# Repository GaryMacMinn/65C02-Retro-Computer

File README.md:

# 65C02-Retro-Computer
A retro computer system based on the 65C02 CPU in a modular format.

This is my first version of a retro 65C02 based comnputer. My original design for this project
was around a single board containing all of the parts (a single board computer!!). After a bit of an
initial draw up, I realised that there were a lot of unknown details to the design and if I needed to change anything it would mean producing an entire new PCB. After a little thought I decided to do a backplane design that allows sections and functionality to be plugged in as required. If I wanted to remove or change any
sections I could just redo that plug in card rather that everything. 

The system at present consists of:
* Backplane Board
* Power Supply and Reset Card
* CPU Card
* Memory Card (Combined Flash Memory and SRAM)
* Serial Card
* Parallel Card

The files included in the Schematic & PCB directory are the KiCAD schematic and PCB files as they stand
at the moment. These cards have been finalised, produced and tested. The others will be added as I build
and verify their designs.

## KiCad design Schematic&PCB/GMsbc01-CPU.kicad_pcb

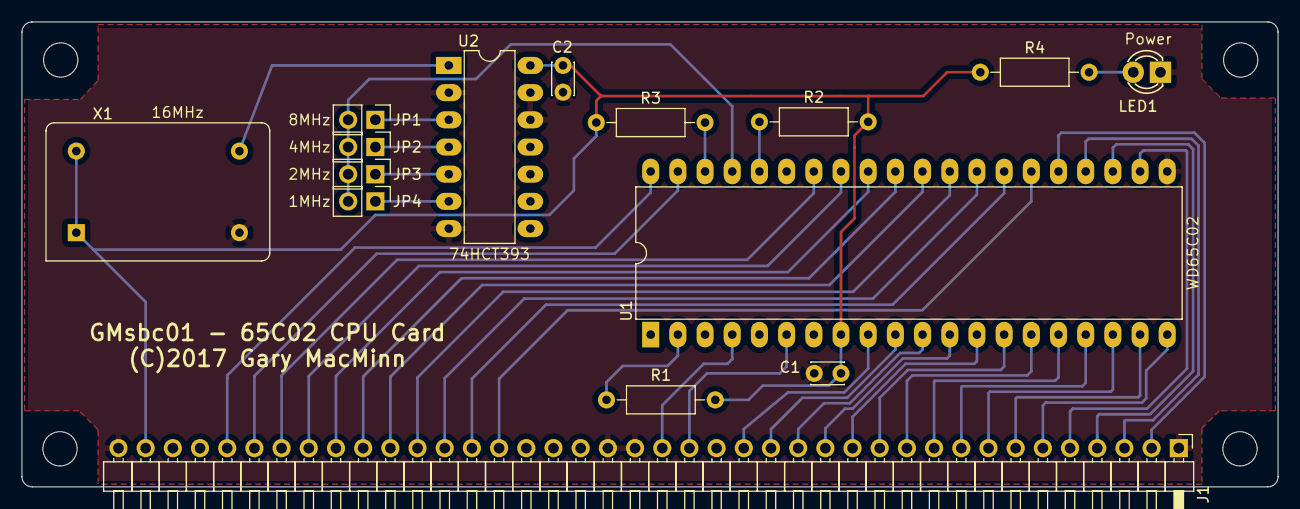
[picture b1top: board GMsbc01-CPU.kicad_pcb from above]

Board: 2 copper layers, 117.3 x 43.4 mm, 19 parts (0 on the bottom side), 41 nets.

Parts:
1, 2, 3, 4: MountingHole_3.2mm_M3
C1, C2: 0.1uF; C_Disc_D3.0mm_W2.0mm_P2.50mm
J1: CONN_01X40; Pin_Header_Angled_1x40_Pitch2.54mm
JP1: 8MHz; Pin_Header_Straight_1x02_Pitch2.54mm
JP2: 4MHz; Pin_Header_Straight_1x02_Pitch2.54mm
JP3: 2MHz; Pin_Header_Straight_1x02_Pitch2.54mm
JP4: 1MHz; Pin_Header_Straight_1x02_Pitch2.54mm
LED1: Power; LED-3MM
R1, R2, R3: 3k3; R_Axial_DIN0207_L6.3mm_D2.5mm_P10.16mm_Horizontal
R4: 330R; R_Axial_DIN0207_L6.3mm_D2.5mm_P10.16mm_Horizontal
U1: WD65C02; DIP-40_W15.24mm_LongPads
U2: 74HCT393; DIP-14_W7.62mm_LongPads
X1: 16MHz; Oscillator_DIP-14

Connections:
+5v: C1.1, C2.1, J1.39, R1.2, R2.2, R3.2, R4.2, U1.8, U2.14, X1.1, X1.14
/IRQ: J1.20, U1.4
/NMI: J1.19, U1.6
/Reset: J1.36, U1.40
A0: J1.17, U1.9
A1: J1.16, U1.10
A2: J1.15, U1.11
A3: J1.14, U1.12
A4: J1.13, U1.13
A5: J1.12, U1.14
A6: J1.11, U1.15
A7: J1.10, U1.16
A8: J1.9, U1.17
A9: J1.8, U1.18
A10: J1.7, U1.19
A11: J1.6, U1.20
A12: J1.5, U1.22
A13: J1.4, U1.23
A14: J1.3, U1.24
A15: J1.2, U1.25
D0: J1.33, U1.33
D1: J1.32, U1.32
D2: J1.31, U1.31
D3: J1.30, U1.30
D4: J1.29, U1.29
D5: J1.28, U1.28
D6: J1.27, U1.27
D7: J1.26, U1.26
GND: C1.2, C2.2, J1.1, J1.21, J1.22, J1.40, LED1.1, U1.21, U2.2, U2.7, U2.12, U2.13, X1.7
unnamed: JP1.1, U2.3
unnamed: JP2.1, U2.4
unnamed: JP3.1, U2.5
unnamed: JP4.1, U2.6
unnamed: LED1.2, R4.1
unnamed: R1.1, U1.2
unnamed: R2.1, U1.36
unnamed: R3.1, U1.38
unnamed: U2.1, X1.8
Phi2: J1.35, U1.39
Phi2In: JP1.2, JP2.2, JP3.2, JP4.2, U1.37
R/-W: J1.34, U1.34

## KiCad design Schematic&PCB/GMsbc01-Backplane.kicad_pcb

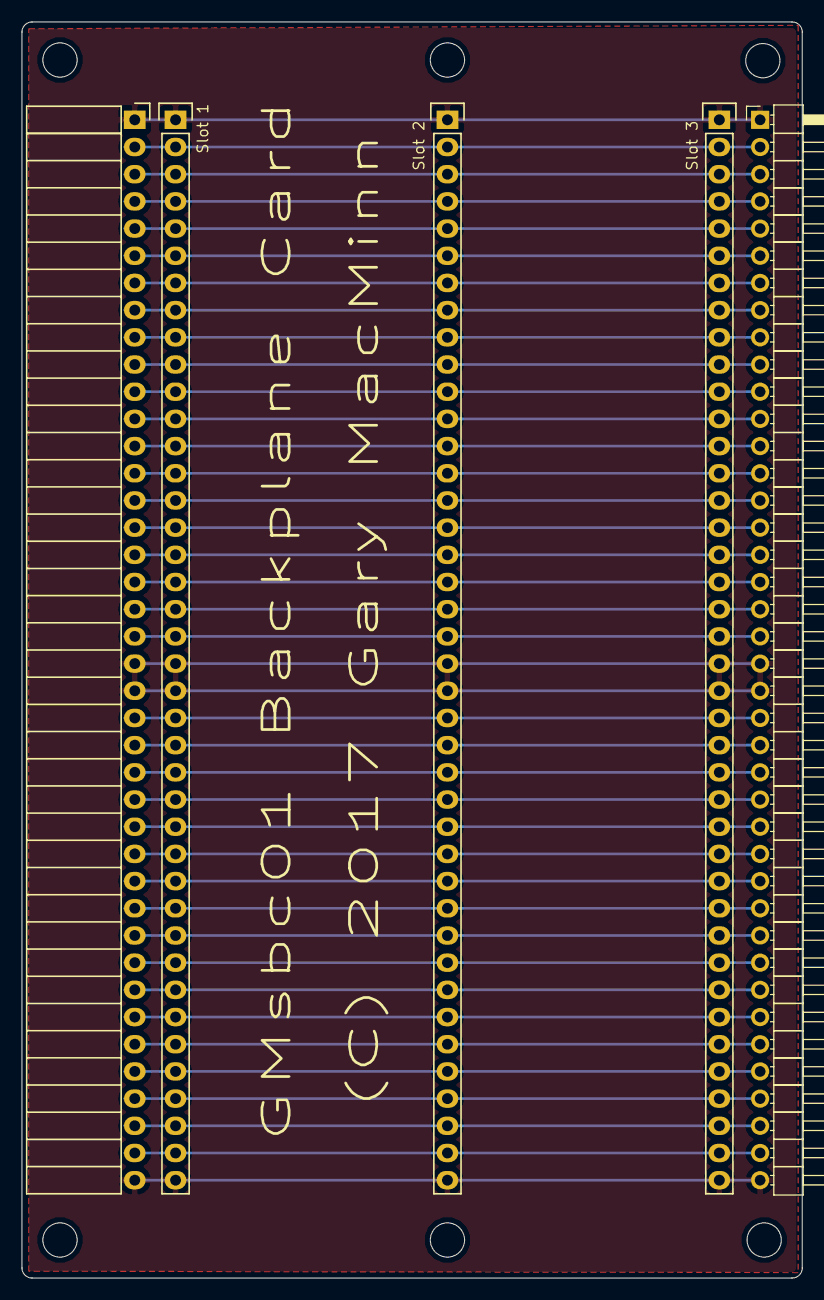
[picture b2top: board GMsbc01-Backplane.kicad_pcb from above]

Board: 2 copper layers, 72.9 x 117.3 mm, 11 parts (0 on the bottom side), 37 nets.

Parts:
1, 2, 3, 7, 8, 9: MountingHole_3.2mm_M3
J1: Slot 4; Socket_Strip_Angled_1x40
J2: Slot 1; Socket_Strip_Straight_1x40
J3: Slot 2; Socket_Strip_Straight_1x40
J4: Slot 3; Socket_Strip_Straight_1x40
J5: Slot 5; Pin_Header_Angled_1x40_Pitch2.54mm

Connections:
+5v: J1.39, J2.39, J3.39, J4.39, J5.39
/IRQ: J1.20, J2.20, J3.20, J4.20, J5.20
/NMI: J1.19, J2.19, J3.19, J4.19, J5.19
/Reset: J1.36, J2.36, J3.36, J4.36, J5.36
A0: J1.17, J2.17, J3.17, J4.17, J5.17
A1: J1.16, J2.16, J3.16, J4.16, J5.16
A2: J1.15, J2.15, J3.15, J4.15, J5.15
A3: J1.14, J2.14, J3.14, J4.14, J5.14
A4: J1.13, J2.13, J3.13, J4.13, J5.13
A5: J1.12, J2.12, J3.12, J4.12, J5.12
A6: J1.11, J2.11, J3.11, J4.11, J5.11
A7: J1.10, J2.10, J3.10, J4.10, J5.10
A8: J1.9, J2.9, J3.9, J4.9, J5.9
A9: J1.8, J2.8, J3.8, J4.8, J5.8
A10: J1.7, J2.7, J3.7, J4.7, J5.7
A11: J1.6, J2.6, J3.6, J4.6, J5.6
A12: J1.5, J2.5, J3.5, J4.5, J5.5
A13: J1.4, J2.4, J3.4, J4.4, J5.4
A14: J1.3, J2.3, J3.3, J4.3, J5.3
A15: J1.2, J2.2, J3.2, J4.2, J5.2
D0: J1.33, J2.33, J3.33, J4.33, J5.33
D1: J1.32, J2.32, J3.32, J4.32, J5.32
D2: J1.31, J2.31, J3.31, J4.31, J5.31
D3: J1.30, J2.30, J3.30, J4.30, J5.30
D4: J1.29, J2.29, J3.29, J4.29, J5.29
D5: J1.28, J2.28, J3.28, J4.28, J5.28
D6: J1.27, J2.27, J3.27, J4.27, J5.27
D7: J1.26, J2.26, J3.26, J4.26, J5.26
GND: J1.1, J1.21, J1.22, J1.40, J2.1, J2.21, J2.22, J2.40, J3.1, J3.21, J3.22, J3.40, J4.1, J4.21, J4.22, J4.40, J5.1, J5.21, J5.22, J5.40
Phi2: J1.35, J2.35, J3.35, J4.35, J5.35
R/-W: J1.34, J2.34, J3.34, J4.34, J5.34
Spare1: J1.18, J2.18, J3.18, J4.18, J5.18
Spare2: J1.23, J2.23, J3.23, J4.23, J5.23
Spare3: J1.24, J2.24, J3.24, J4.24, J5.24
Spare4: J1.25, J2.25, J3.25, J4.25, J5.25
Spare5: J1.37, J2.37, J3.37, J4.37, J5.37
Spare6: J1.38, J2.38, J3.38, J4.38, J5.38

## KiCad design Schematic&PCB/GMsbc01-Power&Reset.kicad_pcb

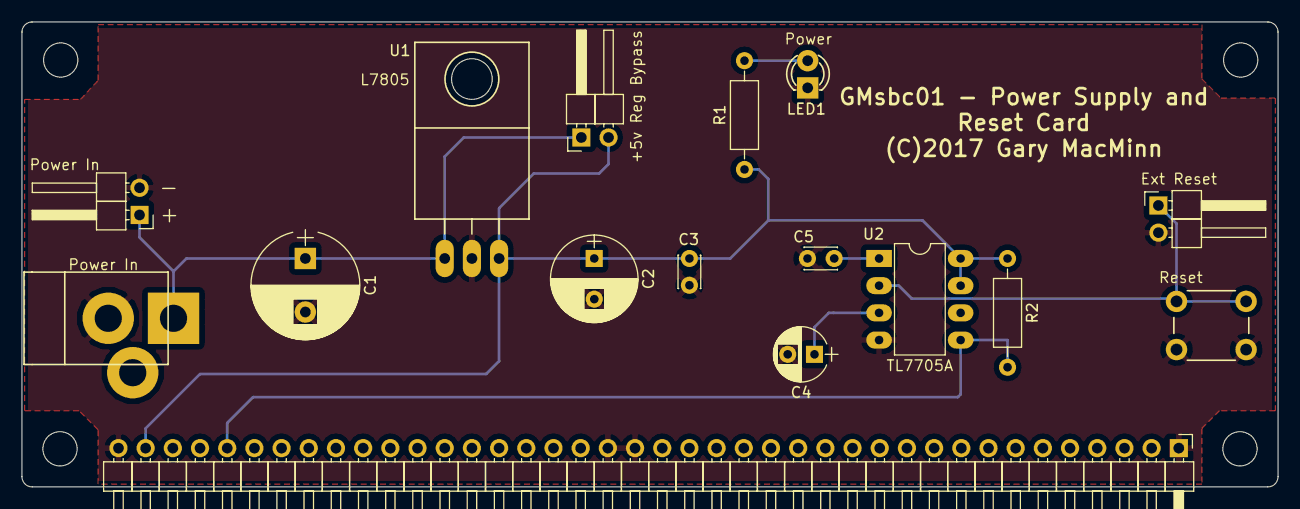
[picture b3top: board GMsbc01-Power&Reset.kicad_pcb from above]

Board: 2 copper layers, 117.3 x 43.4 mm, 20 parts (0 on the bottom side), 8 nets.

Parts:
1, 2, 3, 4: MountingHole_3.2mm_M3
C1: 1000uF 25v; CP_Radial_D10.0mm_P5.00mm
C2: 470uF 16v; CP_Radial_D8.0mm_P3.80mm
C3, C5: 0.1uF; C_Disc_D3.0mm_W2.0mm_P2.50mm
C4: 100uF 16v; CP_Radial_D5.0mm_P2.50mm
J1: Slot 1; Pin_Header_Angled_1x40_Pitch2.54mm
J2: Power In; JACK_ALIM
J3: Power In; Pin_Header_Angled_1x02_Pitch2.54mm
J4: Ext Reset; Pin_Header_Angled_1x02_Pitch2.54mm
JP1: +5v Reg Bypass; Pin_Header_Angled_1x02_Pitch2.54mm
LED1: Power; LED-3MM
R1: 330R; R_Axial_DIN0207_L6.3mm_D2.5mm_P10.16mm_Horizontal
R2: 10k; R_Axial_DIN0207_L6.3mm_D2.5mm_P10.16mm_Horizontal
SW1: Reset; SW_PUSH_6mm
U1: L7805; TO-220_Neutral123_Horizontal_LargePads
U2: TL7705A; DIP-8_W7.62mm_LongPads

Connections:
+5v: C2.1, C3.1, J1.39, JP1.2, R1.1, R2.1, U1.3, U2.7, U2.8
/Reset: J1.36, R2.2, U2.5
GND: C1.2, C2.2, C3.2, C4.2, C5.2, J1.1, J1.21, J1.22, J1.40, J2.2, J3.2, J4.2, LED1.1, SW1.1, U1.2, U2.4
unnamed: C1.1, J2.1, J3.1, JP1.1, U1.1
unnamed: C4.1, U2.3
unnamed: C5.1, U2.1
unnamed: J4.1, SW1.2, U2.2
unnamed: LED1.2, R1.2

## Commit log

2017-10-08 Initial push of backplane, power & CPU cards
2017-10-08 Minor update to README.md file.
2017-10-08 Fixed spelling mistakes in README.md file.

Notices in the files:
Schematic&PCB/GMsbc01-Backplane.kicad_pcb:
(C) 2017 Gary MacMinn
